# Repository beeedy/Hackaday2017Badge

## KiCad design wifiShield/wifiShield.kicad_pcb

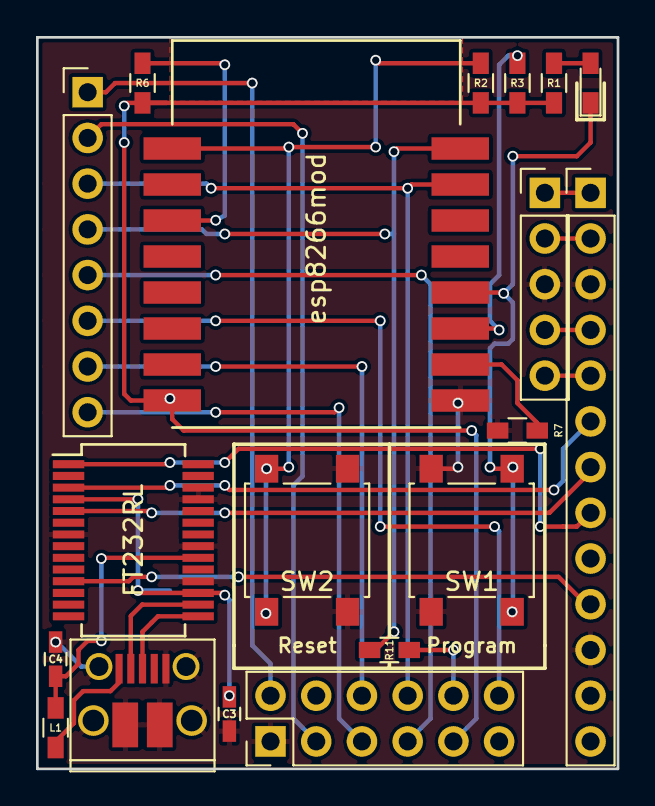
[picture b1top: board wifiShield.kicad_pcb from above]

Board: 2 copper layers, 32.3 x 40.6 mm, 19 parts (0 on the bottom side), 30 nets.

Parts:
C3: 10n; C_0603_HandSoldering
C4: 10u; C_0603_HandSoldering
D1: LED; LED_0603_HandSoldering
J1: USB_OTG; USB_Micro-B_10103594-0001LF
J2: CONN_02X06; Pin_Header_Straight_2x06_Pitch2.54mm
J3: CONN_01X13; Pin_Header_Straight_1x13_Pitch2.54mm
J4: CONN_01X05; Pin_Header_Straight_1x05_Pitch2.54mm
J7: CONN_01X08; Pin_Header_Straight_1x08_Pitch2.54mm
L1: Ferrite_Bead; R_0603_HandSoldering
R1: 1K; R_0603_HandSoldering
R2, R3, R6, R7: 10K; R_0603_HandSoldering
R11: 2K2; R_0603_HandSoldering
SW1, SW2: SW_Push; SW_SPST_B3S-1000
U2: FT232RL; SSOP-28_5.3x10.2mm_Pitch0.65mm
U3: esp8266mod

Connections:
+3V3: J2.9, R1.1, R2.1, R3.1, R6.1, U3.8
+5V: C4.1, L1.2, U2.20
CH_PD: R6.2, U3.3
GND: C3.2, C4.2, J1.5, J1.6, J2.1, J3.3, J3.11, J4.3, R7.2, SW1.1, SW2.1, U2.7, U2.18, U2.21, U2.25, U2.26, U3.9
GPIO0: D1.1, SW1.2, U3.12
GPIO2: R3.2, U3.11
GPIO15: R7.1, U3.10
ISP_C: J3.5, J4.5
ISP_D: J3.4, J4.4
ISP_M: J3.1, J4.1
ISP_V: J3.2, J4.2
unnamed: C3.1, U2.4, U2.17
unnamed: D1.2, R1.2
unnamed: J1.1, L1.1
unnamed: J1.2, U2.16
unnamed: J1.3, U2.15
unnamed: J2.10, R11.2
RA2: J2.5, J7.8
RB0: J2.7, J7.5
RB1: J2.12, J7.6
RB4: J2.6, J7.7
RESET: R2.2, SW2.2, U3.1
RXD: J2.8, J7.3, U3.15
SCL: J2.3, J7.2
SDA: J2.2, J7.1
TTL_CTS: J3.10, U2.11
TTL_RTS: J3.6, U2.3
TTL_RX: J3.7, U2.5
TTL_TX: J3.8, U2.1
TXD: J7.4, R11.1, U3.16

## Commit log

2017-10-15 Init addition of wifi shield files
2017-10-15 Remove extra via and add REV to board
    Board Rev bumped to Rev B
